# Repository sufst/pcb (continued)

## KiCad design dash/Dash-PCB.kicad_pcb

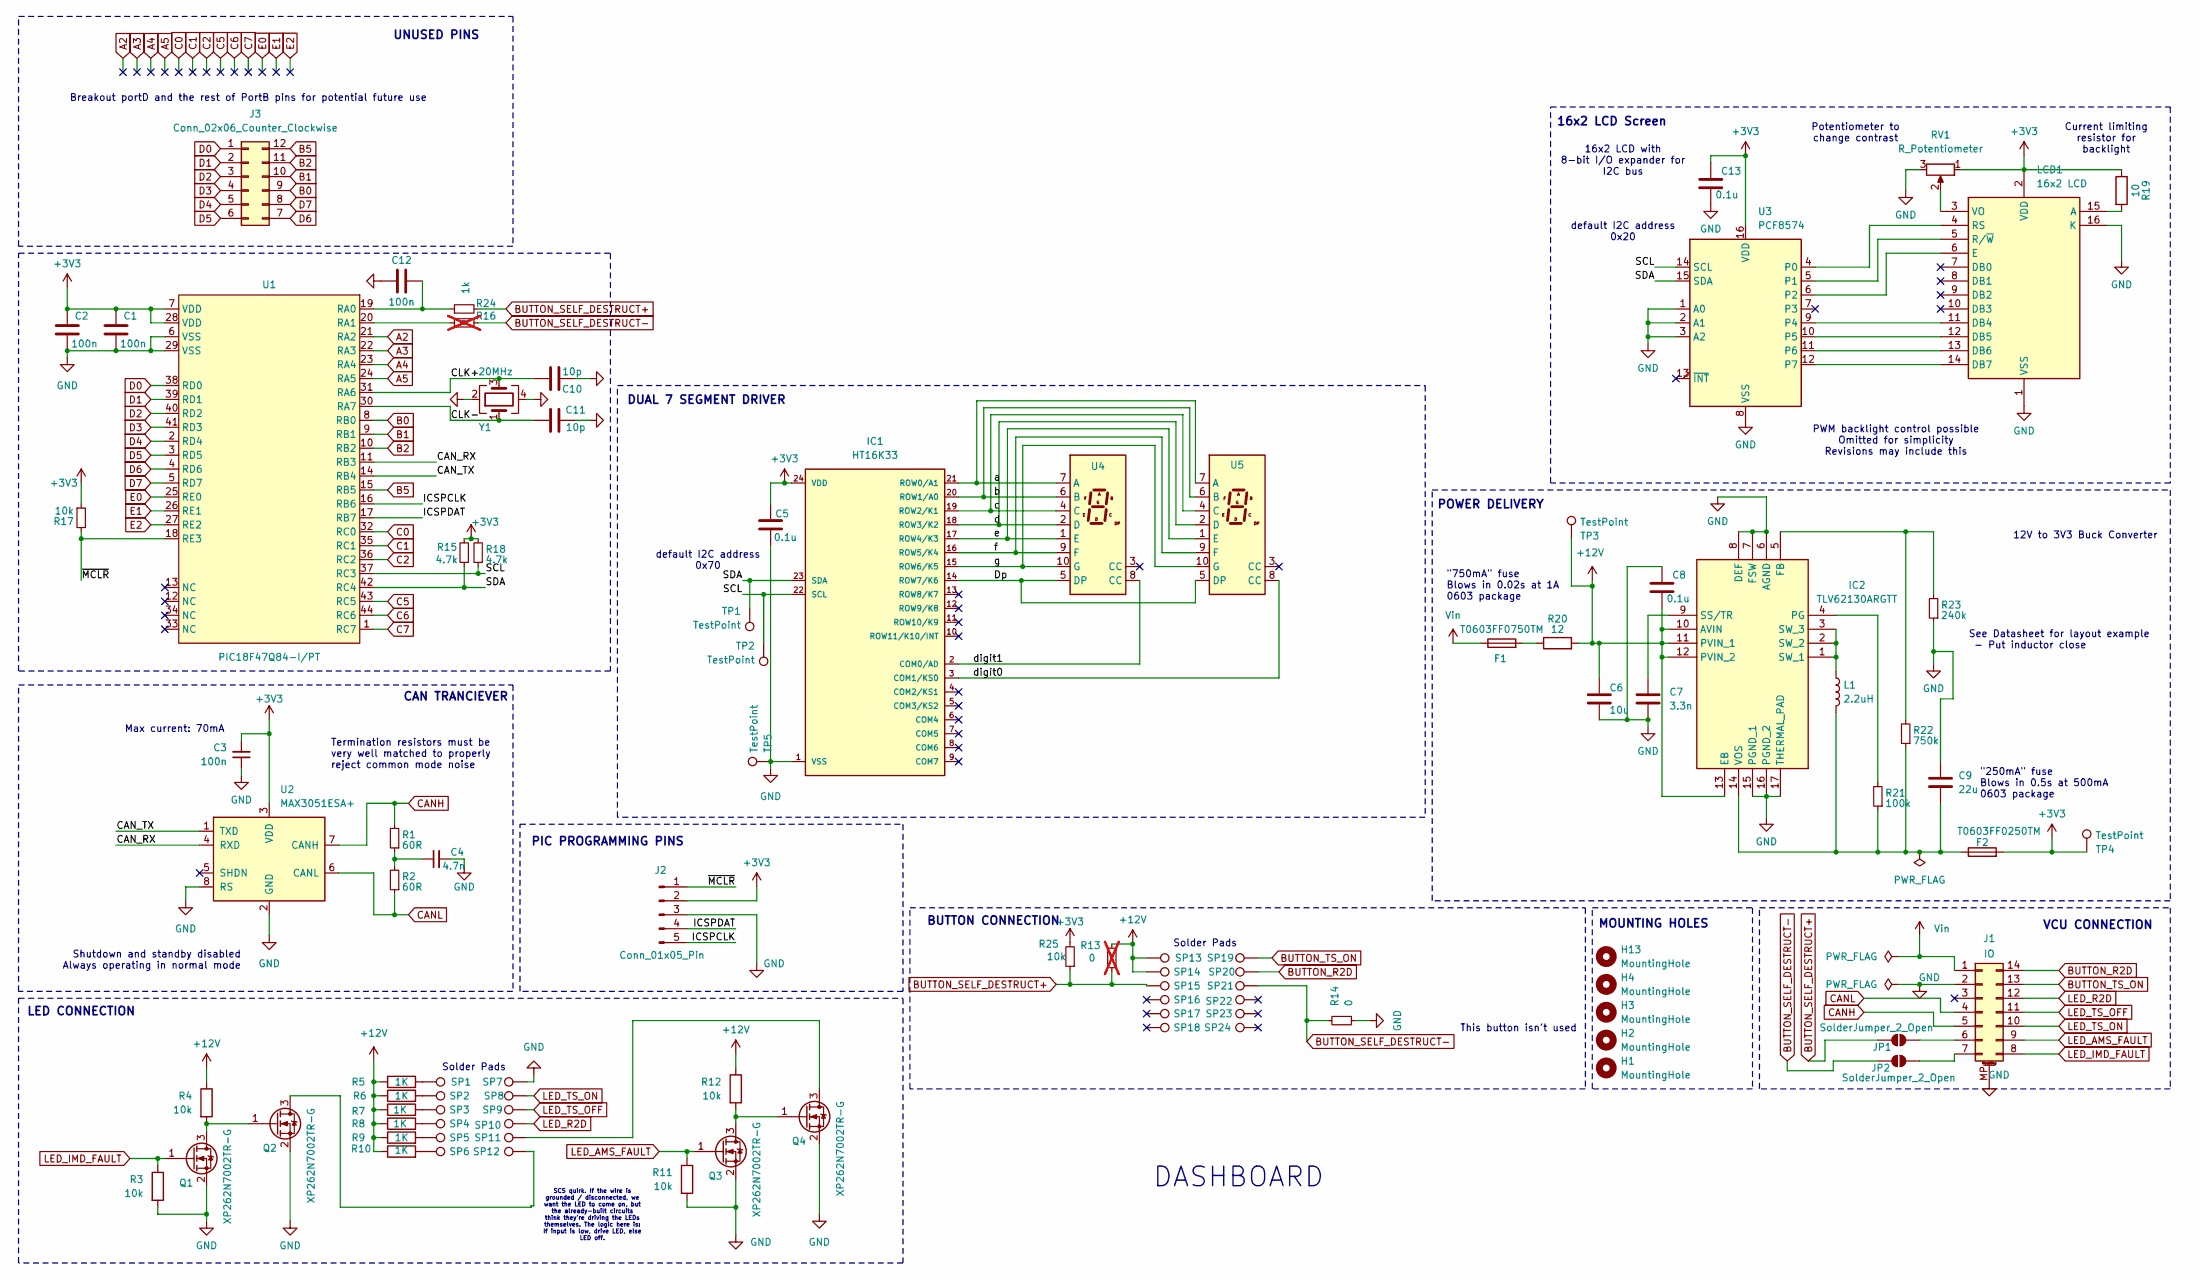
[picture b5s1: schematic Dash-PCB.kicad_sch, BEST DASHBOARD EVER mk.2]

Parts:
C1, C2, C3: 100n; C_0805_2012Metric_Pad1.18x1.45mm_HandSolder
C4: 4.7n; C_0805_2012Metric_Pad1.18x1.45mm_HandSolder
C5, C8, C13: 0.1u; C_0805_2012Metric_Pad1.18x1.45mm_HandSolder
C6: 10u; C_0805_2012Metric_Pad1.18x1.45mm_HandSolder
C7: 3.3n; C_0805_2012Metric_Pad1.18x1.45mm_HandSolder
C9: 22u; C_0805_2012Metric_Pad1.18x1.45mm_HandSolder
C10, C11: 10p; C_0603_1608Metric_Pad1.08x0.95mm_HandSolder; Manufacturer_Part_Number C0805C100J1RACAUTO; Mouser Part Number 80-C0805C100J1RAUTO
C12: 100n; C_0603_1608Metric_Pad1.08x0.95mm_HandSolder; Manufacturer_Part_Number C0805C100J1RACAUTO; Mouser Part Number 80-C0805C100J1RAUTO
F1: T0603FF0750TM; Fuse_0603_1608Metric_Pad1.05x0.95mm_HandSolder
F2: T0603FF0250TM; Fuse_0603_1608Metric_Pad1.05x0.95mm_HandSolder
H1, H2, H3, H4, H13: MountingHole; MountingHole_4.3mm_M4
IC1: HT16K33
IC2: TLV62130ARGTT; QFN50P300X300X100-17N-D; Mouser Part Number 595-TLV62130ARGTT
J1: IO; Molex_Micro-Fit_3.0_43045-1418_2x07-1MP_P3.00mm_Vertical
J2: Conn_01x05_Pin; PinSocket_1x05_P2.54mm_Vertical
J3: Conn_02x06_Counter_Clockwise; PinHeader_2x06_P2.54mm_Vertical
JP1, JP2: SolderJumper_2_Open; SolderJumper-2_P1.3mm_Open_RoundedPad1.0x1.5mm
L1: 2.2uH; IHLP1212BZEV2R2M11
LCD1: 16x2 LCD; Mouser Part Number 426-FIT0127
Q1, Q2, Q3, Q4: XP262N7002TR-G; SOT-23
R1, R2: 60R; R_0805_2012Metric_Pad1.20x1.40mm_HandSolder
R3, R4, R11, R12, R17, R25: 10k; R_0805_2012Metric_Pad1.20x1.40mm_HandSolder
R5, R6, R7, R8, R9, R10: 1K; R_0805_2012Metric_Pad1.20x1.40mm_HandSolder
R13, R16: 0; R_0805_2012Metric_Pad1.20x1.40mm_HandSolder; not fitted
R14: 0; R_0805_2012Metric_Pad1.20x1.40mm_HandSolder
R15, R18: 4.7k; R_0805_2012Metric_Pad1.20x1.40mm_HandSolder
R19: 10; R_0805_2012Metric_Pad1.20x1.40mm_HandSolder
R20: 12; R_0805_2012Metric_Pad1.20x1.40mm_HandSolder
R21: 100k; R_0805_2012Metric_Pad1.20x1.40mm_HandSolder
R22: 750k; R_0805_2012Metric_Pad1.20x1.40mm_HandSolder
R23: 240k; R_0805_2012Metric_Pad1.20x1.40mm_HandSolder
R24: 1k; R_0805_2012Metric_Pad1.20x1.40mm_HandSolder
RV1: R_Potentiometer; TS7Y103KR32
SP1, SP2, SP3, SP4, SP5, SP6, SP7, SP8, SP9, SP10, SP11, SP12, SP13, SP14, SP15, SP16, SP17, SP18, SP19, SP20, SP21, SP22, SP23, SP24: Solder Pad; TestPoint_Pad_D2.0mm
TP1, TP2, TP3, TP4, TP5: TestPoint; TestPoint_THTPad_D2.5mm_Drill1.2mm
U1: PIC18F47Q84-I/PT; TQFP-44_10x10mm_P0.8mm
U2: MAX3051ESA+; SOIC-8_3.9x4.9mm_P1.27mm
U3: PCF8574; SOIC127P1030X265-16N
U4, U5: Generic 7 seg 20mmx27.7mm
Y1: 20MHz; Crystal_SMD_SeikoEpson_FA128-4Pin_2.0x1.6mm; Manufacturer_Part_Number FA-128 20.00M-A0AAYYG80RE0; Mouser Part Number 732-FA12820A0AAYYG80

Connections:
+3V3: C1.1, C2.1, C3.2, C5.1, C13.1, F2.2, IC1.24 (VDD), J2.2, LCD1.2 (VDD), R15.2, R17.1, R18.2, R19.1, R25.2, RV1.1, TP4.1, U1.7 (VDD), U1.28 (VDD), U2.3 (VDD), U3.16 (VDD)
+12V: C6.1, C8.2, IC2.10 (AVIN), IC2.11 (PVIN_1), IC2.12 (PVIN_2), IC2.13 (EB), R4.1, R5.1, R6.1, R7.1, R8.1, R9.1, R10.1, R12.1, R13.2, R20.2, SP13.1, SP14.1, TP3.1
/CAN_RX: U1.11 (RB3), U2.4 (RXD)
/CAN_TX: U1.14 (RB4), U2.1 (TXD)
/CLK+: C10.1, U1.31 (RA6), Y1.3
/CLK-: C11.1, U1.30 (RA7), Y1.1
/Dp: IC1.14 (ROW7/K6), U4.5 (DP), U5.5 (DP)
/ICSPCLK: J2.5, U1.16 (RB6)
/ICSPDAT: J2.4, U1.17 (RB7)
/SCL: IC1.22 (SCL), R18.1, TP2.1, U1.37 (RC3), U3.14 (SCL)
/SDA: IC1.23 (SDA), R15.1, TP1.1, U1.42 (RC4), U3.15 (SDA)
/a: IC1.21 (ROW0/A1), U4.7 (A), U5.7 (A)
/b: IC1.20 (ROW1/A0), U4.6 (B), U5.6 (B)
/c: IC1.19 (ROW2/K1), U4.4 (C), U5.4 (C)
/d: IC1.18 (ROW3/K2), U4.2 (D), U5.2 (D)
/digit0: IC1.3 (COM1/KS0), U5.8 (CC)
/digit1: IC1.2 (COM0/AD), U4.8 (CC)
/e: IC1.17 (ROW4/K3), U4.1 (E), U5.1 (E)
/f: IC1.16 (ROW5/K4), U4.9 (F), U5.9 (F)
/g: IC1.15 (ROW6/K5), U4.10 (G), U5.10 (G)
/~MCLR: J2.1, R17.2, U1.18 (RE3)
A2: U1.21 (RA2)
A3: U1.22 (RA3)
A4: U1.23 (RA4)
A5: U1.24 (RA5)
B0: J3.9, U1.8 (RB0)
B1: J3.10, U1.9 (RB1)
B2: J3.11, U1.10 (RB2)
B5: J3.12, U1.15 (RB5)
BUTTON_R2D: J1.14, SP20.1
BUTTON_SELF_DESTRUCT+: JP1.1 (A), R13.1, R24.2, R25.1, SP15.1
BUTTON_SELF_DESTRUCT-: JP2.1 (A), R14.2, R16.2, SP21.1
BUTTON_TS_ON: J1.13, SP19.1
C0: U1.32 (RC0)
C1: U1.35 (RC1)
C2: U1.36 (RC2)
C5: U1.43 (RC5)
C6: U1.44 (RC6)
C7: U1.1 (RC7)
CANH: J1.5, R1.2, U2.7 (CANH)
CANL: J1.4, R2.1, U2.6 (CANL)
D0: J3.1, U1.38 (RD0)
D1: J3.2, U1.39 (RD1)
D2: J3.3, U1.40 (RD2)
D3: J3.4, U1.41 (RD3)
D4: J3.5, U1.2 (RD4)
D5: J3.6, U1.3 (RD5)
D6: J3.7, U1.4 (RD6)
D7: J3.8, U1.5 (RD7)
E0: U1.25 (RE0)
E1: U1.26 (RE1)
E2: U1.27 (RE2)
GND: C1.2, C2.2, C3.1, C4.2, C5.2, C6.2, C7.2, C8.1, C9.1, C10.2, C11.2, C12.2, C13.2, IC1.1 (VSS), IC2.6 (AGND), IC2.7 (FSW), IC2.8 (DEF), IC2.15 (PGND_1), IC2.16 (PGND_2), IC2.17 (THERMAL_PAD), J1.2, J1.MP (MountPin), J2.3, LCD1.1 (VSS), LCD1.16 (K), Q1.2 (S), Q2.2 (S), Q3.2 (S), Q4.2 (S), R3.2, R11.2, R14.1, R23.1, RV1.3, SP7.1, TP5.1, U1.6 (VSS), U1.29 (VSS), U2.2 (GND), U2.8 (RS), U3.1 (A0), U3.2 (A1), U3.3 (A2), U3.8 (VSS), Y1.2, Y1.4
LED_AMS_FAULT: J1.9, Q3.1 (G), R11.1
LED_IMD_FAULT: J1.8, Q1.1 (G), R3.1
LED_R2D: J1.12, SP10.1
LED_TS_OFF: J1.11, SP9.1
LED_TS_ON: J1.10, SP8.1
unnamed: C4.1, R1.1, R2.2
unnamed: F1.2, R20.1
unnamed: IC2.5 (FB), R22.2, R23.2
unnamed: IC2.4 (PG), R21.2
unnamed: C7.1, IC2.9 (SS/TR)
unnamed: IC2.1 (SW_1), IC2.2 (SW_2), IC2.3 (SW_3), L1.1
unnamed: C9.2, F2.1, IC2.14 (VOS), L1.2, R21.1, R22.1
unnamed: J1.6, JP1.2 (B)
unnamed: J1.7, JP2.2 (B)
unnamed: LCD1.15 (A), R19.2
unnamed: LCD1.11 (DB4), U3.9 (P4)
unnamed: LCD1.12 (DB5), U3.10 (P5)
unnamed: LCD1.13 (DB6), U3.11 (P6)
unnamed: LCD1.14 (DB7), U3.12 (P7)
unnamed: LCD1.6 (E), U3.6 (P2)
unnamed: LCD1.4 (RS), U3.4 (P0)
unnamed: LCD1.5 (R/~W), U3.5 (P1)
unnamed: LCD1.3 (VO), RV1.2
unnamed: Q1.3 (D), Q2.1 (G), R4.2
unnamed: Q2.3 (D), SP12.1
unnamed: Q3.3 (D), Q4.1 (G), R12.2
unnamed: Q4.3 (D), SP11.1
unnamed: R5.2, SP1.1
unnamed: R6.2, SP2.1
unnamed: R7.2, SP3.1
unnamed: R8.2, SP4.1
unnamed: R9.2, SP5.1
unnamed: R10.2, SP6.1
unnamed: C12.1, R24.1, U1.19 (RA0)
unnamed: R16.1, U1.20 (RA1)
Vin: F1.1, J1.1

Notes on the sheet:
Solder Pads
default I2C address 0x20
LED CONNECTION
SCS quirk. If the wire is grounded / disconnected, we want the LED to come on, but the already-built circuits think they're driving the LEDs themselves. The logic here is: If input is low, drive LED, else LED off.
MOUNTING HOLES
CAN TRANCIEVER
Current limiting resistor for backlight
"750mA" fuse Blows in 0.02s at 1A 0603 package
VCU CONNECTION
PWM backlight control possible Omitted for simplicity Revisions may include this
"250mA" fuse Blows in 0.5s at 500mA 0603 package
default I2C address 0x70
DUAL 7 SEGMENT DRIVER
POWER DELIVERY
Breakout portD and the rest of PortB pins for potential future use
12V to 3V3 Buck Converter
16x2 LCD with 8-bit I/O expander for I2C bus
BUTTON CONNECTION
This button isn't used
PIC PROGRAMMING PINS
UNUSED PINS
Shutdown and standby disabled Always operating in normal mode
Potentiometer to change contrast
See Datasheet for layout example - Put inductor close
16x2 LCD Screen
Termination resistors must be very well matched to properly reject common mode noise
DASHBOARD
Max current: 70mA

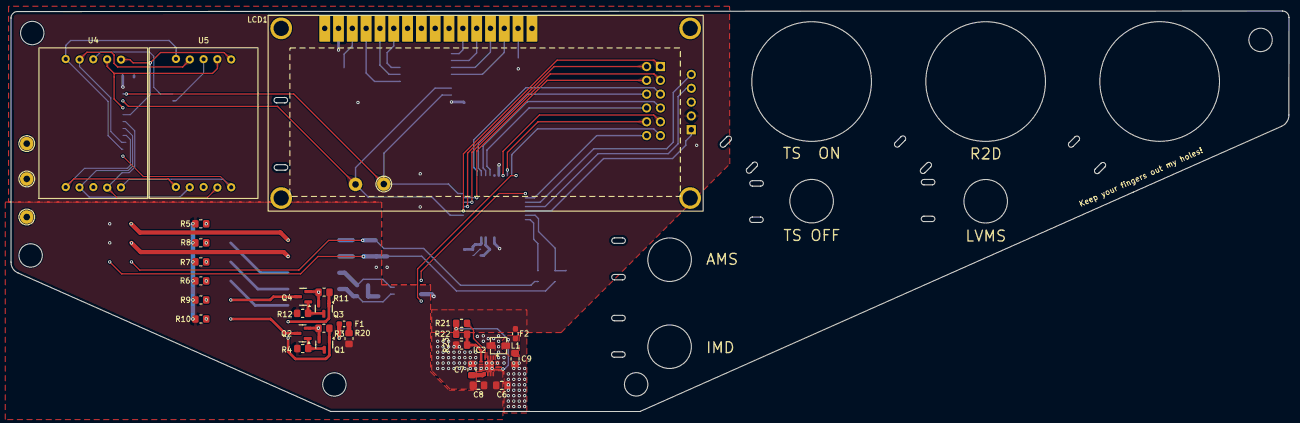
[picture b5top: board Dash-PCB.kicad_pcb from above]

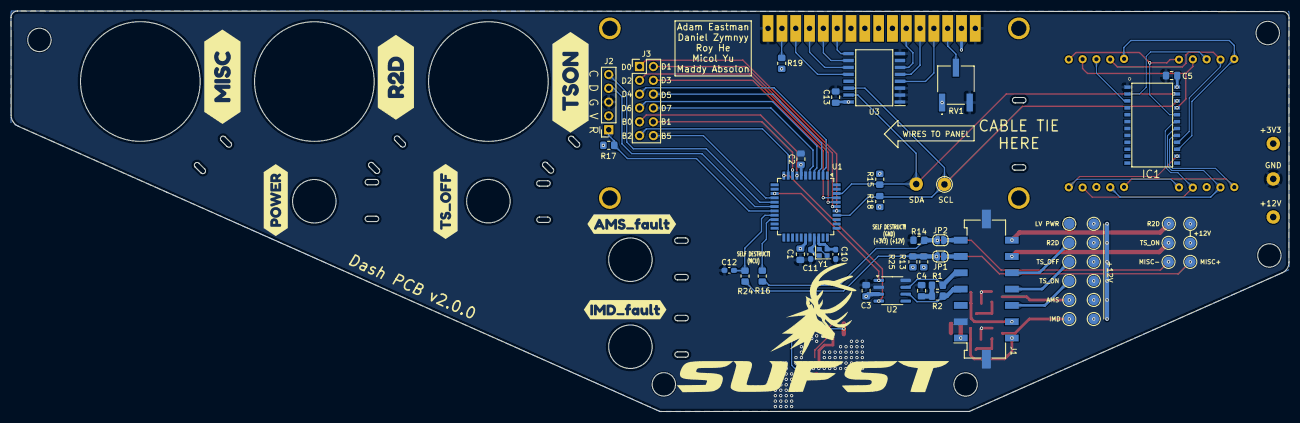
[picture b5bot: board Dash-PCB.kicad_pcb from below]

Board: 2 copper layers, 235.0 x 73.6 mm, 95 parts (57 on the bottom side), 76 nets.

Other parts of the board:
kibuzzard-67F6B156: G***; kibuzzard-67F6B156
kibuzzard-67F52EB7: G***; kibuzzard-67F52EB7
kibuzzard-67F52EF3: G***; kibuzzard-67F52EF3
kibuzzard-67F52FB1: G***; kibuzzard-67F52FB1
kibuzzard-67F52FD7: G***; kibuzzard-67F52FD7
kibuzzard-67F5305C: G***; kibuzzard-67F5305C
kibuzzard-67F53054: G***; kibuzzard-67F53054

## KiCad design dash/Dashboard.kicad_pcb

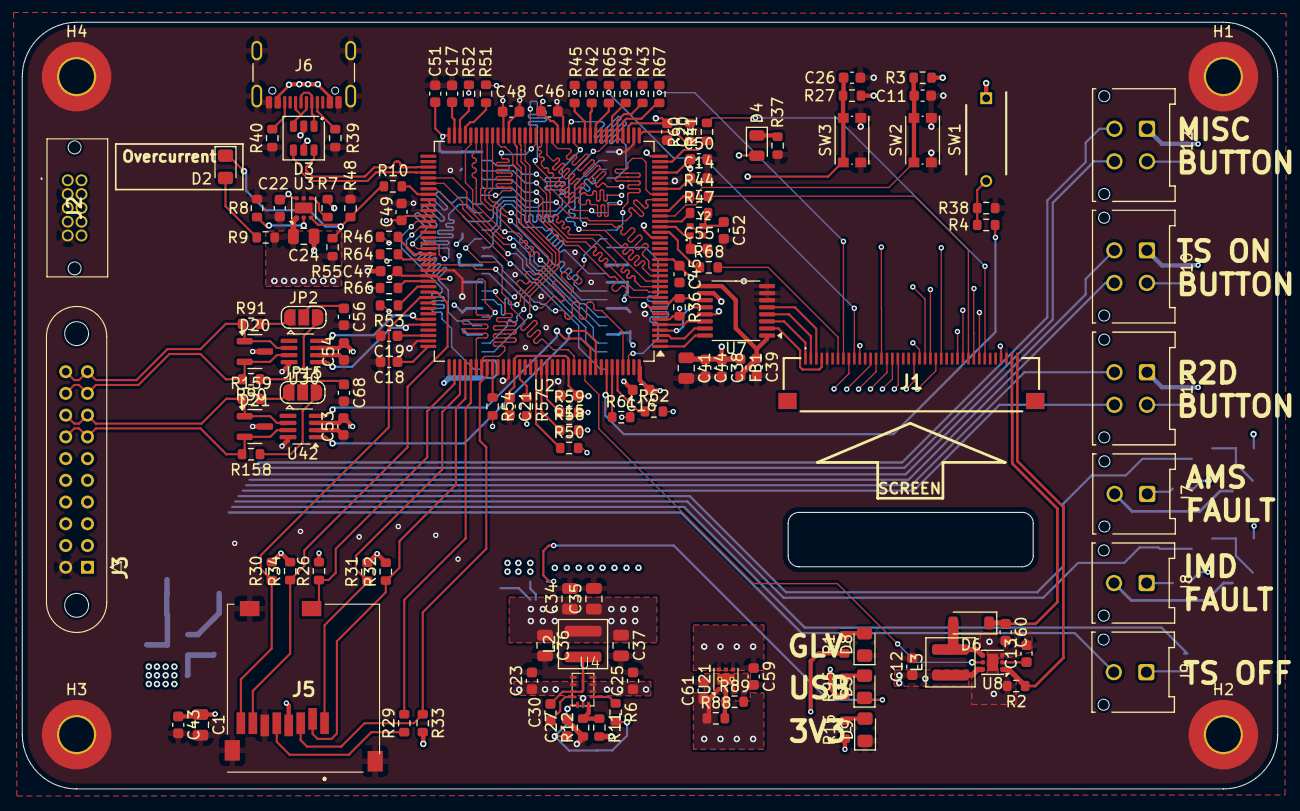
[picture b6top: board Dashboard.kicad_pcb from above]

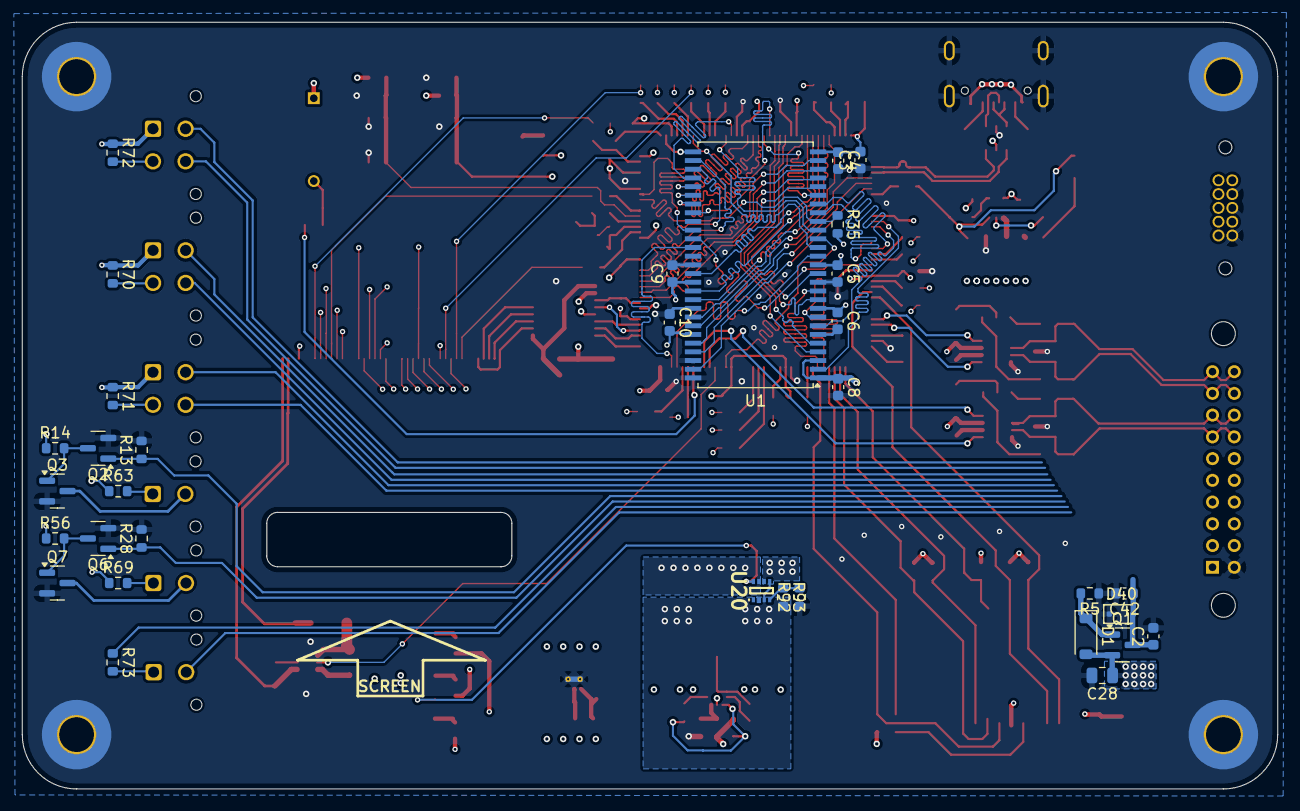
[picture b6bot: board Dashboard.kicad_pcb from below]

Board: 6 copper layers, 115.5 x 70.5 mm, 176 parts (33 on the bottom side), 187 nets.

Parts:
C1, C41: 10u; C_0805_2012Metric
C2, C4, C5, C6, C8, C9, C15, C16, C18, C20, C21, C22, C45, C46, C47, C48, C49, C50, C51: 100nF; C_0603_1608Metric
C3, C10: 2u2; C_0603_1608Metric
C11: 68nF; C_0603_1608Metric
C12, C14: 4.7uF; C_0603_1608Metric
C13, C25: 220nF; C_0603_1608Metric
C17, C19: 2.2u; C_0603_1608Metric
C23: 10uF; C_0603_1608Metric
C24, C34, C35, C36, C37: 22uF; C_0805_2012Metric
C26, C43, C44, C53, C54: 100n; C_0603_1608Metric
C27, C38, C59, C61: 1uF; C_0603_1608Metric
C28: 10uF; C_0805_2012Metric
C30: 0.1uF; C_0603_1608Metric
C39: 10nF; C_0603_1608Metric
C42: 1nF; C_0603_1608Metric
C52, C55: 4.7pF; C_0603_1608Metric
C56, C68: 4.7n; C_0603_1608Metric
C60: 2.2uF; C_0603_1608Metric
D1: BZT52B10; D_SOD-123
D2, D5, D8, D9: LED; LED_0805_2012Metric_Pad1.15x1.40mm_HandSolder
D3: USBLC6-2SC6; SOT-23-6
D4: LED; LED_0805_2012Metric
D6: D_Schottky; D_SOD-123
D20, D21: NUP2105L; SOT-23
D40: D_TVS; D_SOD-323F
FB1: FerriteBead; L_0603_1608Metric
H1, H2, H3, H4: MountingHole_Pad; MountingHole_3.2mm_M3_Pad_TopBottom
J1: XF2M-4015-1A; XF2M40151A
J2: SHF10501LDTHLC
J3: M80-5102042
J5: MEM2061-01-188-00-A; MEM20610118800A
J6: USB_C_Receptacle_USB2.0_16P; USB_C_Receptacle_GCT_USB4105-xx-A_16P_TopMnt_Horizontal
J7, J8, J9: Conn_02x01; Molex_Micro-Fit_3.0_43045-0212_2x01_P3.00mm_Vertical
J10, J11, J12: Conn_02x02_Top_Bottom; Molex_Micro-Fit_3.0_43045-0412_2x02_P3.00mm_Vertical
JP2, JP15: SolderJumper_3_Open; SolderJumper-3_P1.3mm_Open_RoundedPad1.0x1.5mm
L2: 1.5uH; L_Coilcraft_XAL4020-XXX
L3: 10uH; L_Coilcraft_XAL4030-XXX
Q1: DMP510DL-7; SOT-23
Q2, Q3, Q6, Q7: XP262N7002TR-G; SOT-23
R1, R88, R89: 1.5k; R_0603_1608Metric
R2: 3R3; R_0603_1608Metric
R3: 100K; R_0603_1608Metric
R4, R27, R38: 10K; R_0603_1608Metric
R5, R6, R11, R55: 100k; R_0603_1608Metric
R7: 300k; R_0603_1608Metric
R8: 191k; R_0603_1608Metric
R9, R26: 1k; R_0603_1608Metric
R10, R13, R14, R28, R35, R56, R93: 10k; R_0603_1608Metric
R12: 24.9k; R_0603_1608Metric
R15: 150R; R_0603_1608Metric
R29: 22R; R_0603_1608Metric
R30, R31, R32, R33, R34: 47k; R_0603_1608Metric
R36: 50K; R_0603_1608Metric
R37: 200; R_0603_1608Metric
R39, R40: 5.1k; R_0603_1608Metric
R41, R42, R43, R44, R45, R46, R49, R50, R51, R52, R53, R54, R57, R58, R59, R60, R61, R62, R64, R65, R66, R67, R68: 33R; R_0603_1608Metric
R47: 1.3K; R_0603_1608Metric
R48: 20k; R_0603_1608Metric
R63, R69, R70, R71: 220R; R_0603_1608Metric
R72: 1K; R_0603_1608Metric
R73, R95: 330R; R_0603_1608Metric
R90, R91, R158, R159: 60R; R_0603_1608Metric
R92: 90k; R_0603_1608Metric
SW1: SW_SPST; A6T-1101
SW2, SW3: KMR221G LFS; SW_Push_1P1T_NO_CK_KMR2
U1: W9812G6KH-5; TSOP-II-54_22.2x10.16mm_P0.8mm
U2: STM32F746ZGTx; LQFP-144_20x20mm_P0.5mm
U3: TPS25200; WSON-6-1EP_2x2mm_P0.65mm_EP1x1.6mm
U4: LMR33630CRNX
U7: XPT2046TS; TSSOP-16_4.4x5mm_P0.65mm
U8: TPS61165DRV; WSON-6-1EP_2x2mm_P0.65mm_EP1x1.6mm
U20: TPS2117; SOTFL50P160X60-8N
U21: TLV759P; WSON-6-1EP_2x2mm_P0.65mm_EP1x1.6mm_ThermalVias
U30, U42: TCAN3404-Q1; SOT-23-8_Handsoldering
Y2: 25MHz; Resonator_SMD_ECS_ECX-1247Q_1.6x1.2x0.3mm

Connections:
+3.3VA: C39.1, FB1.2, U7.1 (VCC), U7.9 (VREF)
+3V3: C1.1, C3.2, C4.1, C5.1, C6.1, C8.1, C9.1, C10.2, C14.1, C15.1, C16.1, C18.1, C20.1, C21.1, C38.1, C41.1, C43.1, C44.1, C45.1, C46.1, C47.1, C48.1, C49.1, C50.1, C51.1, C53.2, C54.2, C61.1, FB1.1, J1.37, J2.1 (VTref), J5.P4 (VDD), R3.2, R15.1, R26.2, R27.2, R30.2, R31.2, R32.2, R33.2, R34.2, R35.2, R36.2, R88.1, SW1.1 (A), U1.1 (VDD), U1.3 (VDDQ), U1.9 (VDDQ), U1.14 (VDD), U1.27 (VDD), U1.43 (VDDQ), U1.49 (VDDQ), U2.6 (VBAT), U2.17 (VDD), U2.30 (VDD), U2.33 (VDDA), U2.39 (VDD), U2.52 (VDD), U2.62 (VDD), U2.72 (VDD), U2.84 (VDD), U2.95 (VDDUSB), U2.108 (VDD), U2.121 (VDD), U2.131 (VDD), U2.144 (VDD), U7.10 (IOVDD), U21.1 (OUT), U30.3 (VCC), U42.3 (VCC)
+5V: C12.1, C59.1, L3.1, R95.1, U8.6 (VIN), U20.2 (VOUT), U20.7 (VOUT), U21.4 (EN), U21.6 (IN)
+5V_REG: C34.1, C35.1, C36.1, C37.1, L2.2, R11.2, R93.2, U20.3 (VIN1), U20.5 (MODE)
+5V_USB: C22.1, D3.5 (VP), J6.A4 (VBUS), J6.A9 (VBUS), J6.B4 (VBUS), J6.B9 (VBUS), R7.2, U3.6 (IN)
+5V_USB_PROT: C24.1, R9.1, R55.1, U3.1 (OUT), U20.6 (VIN2)
+GLV: C2.1, C42.1, D40.2 (A2), J3.1, Q1.3 (D)
+GLV_PROT: C23.1, C25.1, C28.1, D1.2 (K), J10.1, J11.1, J12.1, Q1.2 (S), R1.1, R14.1, R56.1, R63.1, R69.1, R70.1, R71.1, R72.1, U4.2 (VIN), U4.9 (EN), U4.10 (VIN)
/I/O/AMS.LED.SIG: J3.3, Q2.1 (G), R13.1
/I/O/AMS_LED_SCS: J7.2, Q3.3 (D)
/I/O/CAN1_RX: U2.103 (PA11), U30.4 (RXD)
/I/O/CAN1_TX: U2.104 (PA12), U30.1 (TXD)
/I/O/CAN2_RX: U2.135 (PB5), U42.4 (RXD)
/I/O/CAN2_TX: U2.136 (PB6), U42.1 (TXD)
/I/O/CAN.C+: D21.2 (K), J3.7, J3.17, R158.2, U42.7 (CANH)
/I/O/CAN.C-: D21.1 (K), J3.8, J3.18, R159.1, U42.6 (CANL)
/I/O/CAN.F+: D20.2 (K), J3.9, J3.19, R90.2, U30.7 (CANH)
/I/O/CAN.F-: D20.1 (K), J3.10, J3.20, R91.1, U30.6 (CANL)
/I/O/IMD.LED.SIG: J3.13, Q6.1 (G), R28.1
/I/O/IMD_LED_SCS: J8.2, Q7.3 (D)
/I/O/R2D.BUTTON.GND: J3.4, J11.3
/I/O/R2D.LED.GND: J3.14, J11.4
/I/O/SPARE.BUTTON.GND: J3.6, J12.3
/I/O/SPARE.LED.GND: J3.16, J12.4
/I/O/TS.ON.BUTTON.GND: J3.5, J10.3
/I/O/TS.ON.LED.GND: J3.15, J10.4
/I/O/TSAL.DASH.EXC: J3.2, R73.1
/I/O/TSAL.GREEN.DASH.LED.GND: J3.12, J9.2
/MCU/BOOT0: R4.1, U2.138 (BOOT0)
/MCU/LCD_B2: R57.1, U2.122 (PD6)
/MCU/LCD_B3: R58.1, U2.126 (PG11)
/MCU/LCD_B4: R59.1, U2.127 (PG12)
/MCU/LCD_B5: R60.1, U2.37 (PA3)
/MCU/LCD_B6: R61.1, U2.139 (PB8)
/MCU/LCD_B7: R62.1, U2.140 (PB9)
/MCU/LCD_DCLK: R64.1, U2.92 (PG7)
/MCU/LCD_DE: R68.1, U2.22 (PF10)
/MCU/LCD_DISP: R65.1, U2.45 (PC5)
/MCU/LCD_G2: R49.1, U2.42 (PA6)
/MCU/LCD_G3: R50.1, U2.125 (PG10)
/MCU/LCD_G4: R51.1, U2.69 (PB10)
/MCU/LCD_G5: R52.1, U2.70 (PB11)
/MCU/LCD_G6: R53.1, U2.97 (PC7)
/MCU/LCD_G7: R54.1, U2.117 (PD3)
/MCU/LCD_HSYNC: R66.1, U2.96 (PC6)
/MCU/LCD_R2: R41.1, U2.35 (PA1)
/MCU/LCD_R3: R42.1, U2.46 (PB0)
/MCU/LCD_R4: R43.1, U2.41 (PA5)
/MCU/LCD_R5: R44.1, U2.26 (PC0)
/MCU/LCD_R6: R45.1, U2.47 (PB1)
/MCU/LCD_R7: R46.1, U2.91 (PG6)
/MCU/LCD_VSYNC: R67.1, U2.40 (PA4)
/MCU/LCD_XL: J1.2, U7.4 (XN)
/MCU/LCD_XR: J1.4, U7.2 (XP)
/MCU/LCD_YD: J1.3, U7.5 (YN)
/MCU/LCD_YU: J1.1, U7.3 (YP)
/MCU/OSC_IN: C55.1, U2.23 (PH0), Y2.1
/MCU/OSC_OUT: R47.1, U2.24 (PH1)
/MCU/RAM_A0: U1.23 (A0), U2.10 (PF0)
/MCU/RAM_A1: U1.24 (A1), U2.11 (PF1)
/MCU/RAM_A2: U1.25 (A2), U2.12 (PF2)
/MCU/RAM_A3: U1.26 (A3), U2.13 (PF3)
/MCU/RAM_A4: U1.29 (A4), U2.14 (PF4)
/MCU/RAM_A5: U1.30 (A5), U2.15 (PF5)
/MCU/RAM_A6: U1.31 (A6), U2.50 (PF12)
/MCU/RAM_A7: U1.32 (A7), U2.53 (PF13)
/MCU/RAM_A8: U1.33 (A8), U2.54 (PF14)
/MCU/RAM_A9: U1.34 (A9), U2.55 (PF15)
/MCU/RAM_A10: U1.22 (A10/AP), U2.56 (PG0)
/MCU/RAM_A11: U1.35 (A11), U2.57 (PG1)
/MCU/RAM_BA0: U1.20 (BS0), U2.89 (PG4)
/MCU/RAM_BA1: U1.21 (BS1), U2.90 (PG5)
/MCU/RAM_CAS: U1.17 (~CAS), U2.132 (PG15)
/MCU/RAM_CKE: U1.37 (CKE), U2.29 (PC3)
/MCU/RAM_CLK: U1.38 (CLK), U2.93 (PG8)
/MCU/RAM_CS/NE: R35.1, U1.19 (~CS), U2.28 (PC2)
/MCU/RAM_D0: U1.2 (DQ0), U2.85 (PD14)
/MCU/RAM_D1: U1.7 (DQ3), U2.86 (PD15)
/MCU/RAM_D2: U1.8 (DQ4), U2.114 (PD0)
/MCU/RAM_D3: U1.11 (DQ6), U2.115 (PD1)
/MCU/RAM_D4: U1.4 (DQ1), U2.58 (PE7)
/MCU/RAM_D5: U1.5 (DQ2), U2.59 (PE8)
/MCU/RAM_D6: U1.10 (DQ5), U2.60 (PE9)
/MCU/RAM_D7: U1.13 (DQ7), U2.63 (PE10)
/MCU/RAM_D8: U1.42 (DQ8), U2.64 (PE11)
/MCU/RAM_D9: U1.44 (DQ9), U2.65 (PE12)
/MCU/RAM_D10: U1.45 (DQ10), U2.66 (PE13)
/MCU/RAM_D11: U1.47 (DQ11), U2.67 (PE14)
/MCU/RAM_D12: U1.48 (DQ12), U2.68 (PE15)
/MCU/RAM_D13: U1.50 (DQ13), U2.77 (PD8)
/MCU/RAM_D14: U1.51 (DQ14), U2.78 (PD9)
/MCU/RAM_D15: U1.53 (DQ15), U2.79 (PD10)
/MCU/RAM_NBL0: U1.15 (LDQM), U2.141 (PE0)
/MCU/RAM_NBL1: U1.39 (UDQM), U2.142 (PE1)
/MCU/RAM_RAS: U1.18 (~RAS), U2.49 (PF11)
/MCU/RAM_WE: U1.16 (~WE), U2.43 (PA7)
/MCU/SD_CARD_DETECT: J5.CD1 (DET_A), R26.1, U2.110 (PA15)
/MCU/SD_CK: R29.2, U2.113 (PC12)
/MCU/SD_CMD: J5.P3 (CMD), R33.1, U2.116 (PD2)
/MCU/SD_D0: J5.P7 (DAT0), R34.1, U2.98 (PC8)
/MCU/SD_D1: J5.P8 (DAT1), R30.1, U2.99 (PC9)
/MCU/SD_D2: J5.P1 (DAT2), R31.1, U2.111 (PC10)
/MCU/SD_D3: J5.P2 (DAT3/CD), R32.1, U2.112 (PC11)
/MCU/SPI_CS: U2.3 (PE4), U7.15 (~CS)
/MCU/SPI_MISO: U2.4 (PE5), U7.12 (DOUT)
/MCU/SPI_MOSI: U2.5 (PE6), U7.14 (DIN)
/MCU/SPI_SCK: U2.1 (PE2), U7.16 (DCLK)
/MCU/SWCLK: J2.4 (SWCLK/TCK), U2.109 (PA14)
/MCU/SWDIO: J2.2 (SWDIO/TMS), U2.105 (PA13)
/MCU/SWO: J2.6 (SWO/TDO), U2.133 (PB3)
/MCU/TOUCH_BUSY: U2.8 (PC14), U7.13 (BUSY)
/MCU/TOUCH_IRQ: R36.1, U2.9 (PC15), U7.11 (~PENIRQ)
/MCU/USB_D+: D3.4 (L2), U2.76 (PB15)
/MCU/USB_D-: D3.6 (L1), U2.75 (PB14)
/MCU/nRESET: C11.2, J2.10 (~RESET), R3.1, SW2.1, U2.25 (NRST)
/MCU/rob_led!: D4.2 (A), U2.36 (PA2)
/MCU/user_button: C26.2, R27.1, SW3.1, U2.21 (PF9)
/Power/FAULT_LED: D2.1 (K), R10.2, R48.1, R55.2, U3.3 (~FAULT)
/Power/FB: R11.1, R12.2, U4.7 (FB)
/Power/SW: C30.2, L2.1, U4.3 (NC), U4.12 (SW)
/Power/USB_LED: D5.1 (K), U20.8 (ST)
/Power/VCC: C27.1, R6.2, U4.5 (VCC)
BACKLIGHT_A: C60.1, D6.1 (K), J1.39
BACKLIGHT_K: J1.40, R2.1, U8.1 (FB)
BACKLIGHT_PWM: U2.134 (PB4), U8.5 (CTRL)
GND: C1.2, C2.2, C3.1, C4.2, C5.2, C6.2, C8.2, C9.2, C10.1, C11.1, C12.2, C13.2, C14.2, C15.2, C16.2, C17.2, C18.2, C19.2, C20.2, C21.2, C22.2, C23.2, C24.2, C25.2, C26.1, C27.2, C28.2, C34.2, C35.2, C36.2, C37.2, C38.2, C39.2, C41.2, C42.2, C43.2, C44.2, C45.2, C46.2, C47.2, C48.2, C49.2, C50.2, C51.2, C52.2, C53.1, C54.1, C55.2, C56.2, C59.2, C60.2, C61.2, C68.2, D3.2 (VN), D8.1 (K), D9.1 (K), D20.3 (A), D21.3 (A), D40.1 (A1), H1.1, H2.1, H3.1, H4.1, J1.5, J1.38, J2.3 (GND), J2.5 (GND), J2.9 (GNDDetect), J3.11, J5.CD2 (DET_B), J5.G1 (SHIELD), J5.G2 (SHIELD), J5.P6 (VSS), J6.A1 (GND), J6.A12 (GND), J6.B1 (GND), J6.B12 (GND), J6.S1 (SHIELD), Q2.2 (S), Q3.2 (S), Q6.2 (S), Q7.2 (S), R2.2, R5.1, R8.1, R12.1, R13.2, R28.2, R37.2, R38.2, R39.1, R40.1, R48.2, R89.2, R92.1, SW2.2, SW3.2, U1.6 (VSSQ), U1.12 (VSSQ), U1.28 (VSS), U1.41 (VSS), U1.46 (VSSQ), U1.52 (VSSQ), U1.54 (VSS), U2.16 (VSS), U2.31 (VSSA), U2.38 (VSS), U2.51 (VSS), U2.61 (VSS), U2.83 (VSS), U2.94 (VSS), U2.107 (VSS), U2.120 (VSS), U2.130 (VSS), U3.5 (GND), U3.7 (PAD), U4.1 (PGND), U4.6 (AGND), U4.11 (PGND), U7.6 (GND), U7.7 (VBAT), U7.8 (IN), U8.3 (GND), U8.7 (GND), U20.1 (GND), U21.3 (GND), U21.7 (EX), U30.2 (GND), U30.8 (STB), U42.2 (GND), U42.8 (STB), Y2.2, Y2.4
unnamed: C52.1, R47.2, Y2.3
unnamed: D1.1 (A), Q1.1 (G), R5.2
unnamed: D2.2 (A), R9.2
unnamed: D3.1 (L1), J6.A7 (D-), J6.B7 (D-)
unnamed: D3.3 (L2), J6.A6 (D+), J6.B6 (D+)
unnamed: D4.1 (K), R37.1
unnamed: D5.2 (A), R95.2
unnamed: D6.2 (A), L3.2, U8.4 (SW)
unnamed: D8.2 (A), R1.2
unnamed: D9.2 (A), R15.2
unnamed: J1.7, R68.2
unnamed: J1.8, R67.2
unnamed: J1.9, R66.2
unnamed: J1.10, R65.2
unnamed: J1.11, R64.2
unnamed: J1.13, R62.2
unnamed: J1.14, R61.2
unnamed: J1.15, R60.2
unnamed: J1.16, R59.2
unnamed: J1.17, R58.2
unnamed: J1.18, R57.2
unnamed: J1.21, R54.2
unnamed: J1.22, R53.2
unnamed: J1.23, R52.2
unnamed: J1.24, R51.2
unnamed: J1.25, R50.2
unnamed: J1.26, R49.2
unnamed: J1.29, R46.2
unnamed: J1.30, R45.2
unnamed: J1.31, R44.2
unnamed: J1.32, R43.2
unnamed: J1.33, R42.2
unnamed: J1.34, R41.2
unnamed: J5.P5 (CLK), R29.1
unnamed: J6.A5 (CC1), R39.2
unnamed: J6.B5 (CC2), R40.2
unnamed: J7.1, R63.2
unnamed: J8.1, R69.2
unnamed: J9.1, R73.2
unnamed: J10.2, R70.2
unnamed: J11.2, R71.2
unnamed: J12.2, R72.2
unnamed: JP2.1 (A), R91.2
unnamed: JP2.3 (B), R90.1
unnamed: C56.1, JP2.2 (C)
unnamed: JP15.1 (A), R159.2
unnamed: JP15.3 (B), R158.1
unnamed: C68.1, JP15.2 (C)
unnamed: Q2.3 (D), Q3.1 (G), R14.2
unnamed: Q6.3 (D), Q7.1 (G), R56.2
unnamed: R4.2, R38.1, SW1.2 (B)
unnamed: C17.1, U2.71 (VCAP_1)
unnamed: C19.1, U2.106 (VCAP_2)
unnamed: R7.1, U3.4 (EN)
unnamed: R8.2, U3.2 (ILIM)
unnamed: C30.1, U4.4 (BOOT)
unnamed: R6.1, U4.8 (PG)
unnamed: C13.1, U8.2 (COMP)
unnamed: R92.2, R93.1, U20.4 (PR1)
unnamed: R88.2, R89.1, U21.2 (FB)
~USB_FAULT: R10.1, U2.80 (PD11)
